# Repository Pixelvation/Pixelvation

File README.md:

**Pixelvation enables people to create high-quality LED art using open source tools**

This GitHub repository is the current home of Pixelvation and will be updated whenever there's some significant new development.  To get notified on significant new developments, set up an alert on new releases here, or follow [@PixelvationRGB on Twitter](https://twitter.com/PixelvationRgb).

I'll set up a forum or Discord server at some point, but for now, feel free to open a GitHub Issue, or post to [SmartMatrix Community](https://community.pixelmatix.com) if you have any questions or want to discuss anything.

## Open Source Early

I've released several open source products, where the open source files were published after the product was designed, manufactured, and at a distributor ready to purchase.  With my [latest crowdfunded product](https://www.crowdsupply.com/pixelmatix/smartled-shield-for-teensy-4) I realized how much time I had spent on marketing and logistics while prepping for and running the campaign - work I really dislike - relative to the creative and technical work that I really enjoy.  I also really enjoy sharing my projects and collaborating with other people, but releasing the product through a crowdfunding campaign delayed the start of fully sharing my project details and collaborating with other people by months.

With Pixelvation, I'm trying a new approach to sharing my projects: releasing projects as open source early on - well before I even have plans to release a project as a product - and making it easy for people to source the hardware themselves.  I'm designing my projects around components that are available from [JLCPCB's SMT Library](https://jlcpcb.com/parts) whenever possible, so if you want to try one of the hardware designs you just place an order with JLCPCB for 5+ pieces of assembled PCBs, and they'll be manufactured and shipped for a very reasonable price in under a week.

I'm releasing work-in-progress designs under a CC BY-NC-SA license.  Usually I don't release my designs with a "-NC" Non-Commercial license, and after the design is further along and ready for sale I'll change the license to CC BY-SA.  I'm conflicted about this and may change my mind later as designs released "-NC" aren't truly open source, but for now I'm being conservative and keeping the "-NC".

## Pixelvation Engine

The first tool in development now is the Pixelvation Engine, a small board dedicated to receiving a single stream of LED data via serial, and driving a lot of LEDs with that data.  The Engine will support driving HUB75 panels, or addressable LEDs.

As input, Pixelvation Engine accepts APA102 data at up to 5MHz, with 1-bit serial (like an APA102 LED), or up to 8-bit parallel.  The 1-bit serial input and CLK are buffered to accept up to 5V signals, but the remaining 7-bits parallel data must be driven at 3.3V only.

Pixelvation Engine has 16 outputs buffered to 5V levels, and an extra 3.3V output.  The outputs are arranged around the pinout of a HUB75 panel, so the board can be plugged into a HUB75 panel directly.  To instead drive up to 16 channels of addressable LEDs, Pixelvation Engine needs to be plugged into a simple breakout board.  Generic breakout boards will be designed and released in the future, but you can also design your own project-specific breakout board with space for the Pixelvation Engine, and the form factor and LED connectors your project actually needs.

Pixelvation Engine is based around the ESP32, which has enough RAM, CPU power, and DMA functionality to deal with a lot of LED data, and some unique I2S peripherals that allow for receiving a fast stream of serial or parallel LED data as input, and setting up another stream of parallel LED data as output.

To program Pixelvation Engine you need a USB-Serial adapter.  This functionality was purposely left off the board to save space and cost, and ideally these features are only needed when setting up a project.  The programming pins on the input side were designed around the ESP-01 pinout, so cheap ESP-01 programmers can be used.  Specifically [this ESP-01 programmer](https://www.amazon.com/ESP-01S-Programmer-Adapter-Wireless-4-5-5-5V/dp/B07V556Q82) ([cheaper on Aliexpress](https://www.aliexpress.com/item/32882742790.html))  has the most functionality and is the easiest to use on its own, is widely available, and with a couple jumper wires added becomes even more functional.

### Status

Currently Pixelvation Engine has been tested driving HUB75 panels up to 64x64 pixels, with APA102 input sources from [Pixelblaze (V1-V3)](https://www.crowdsupply.com/hencke-technologies/pixelblaze-v3), [WLED's sound reactive fork](https://github.com/atuline/WLED/) compiled with APA102 output and running on an ESP32 Dev board, and a Fadecandy-inspired USB to APA102 output board currently in development.

Pixelvation Engine uses [SmartMatrix Library 4.0's](https://github.com/pixelmatix/SmartMatrix) ESP32 support for driving HUB75 panels, and is able to drive a 64x64 HUB75 panel with 36-bit color, at 240Hz.  It's possible to drive a 128x64 HUB75 panel with the same color settings, but it requires additional hardware outside the Pixelvation Engine (this is being prototyped now).

The addressable LED output functionality hasn't been tested yet.  

The I2S Input code has some room for improvement, as it's very inefficient with memory right now, and can't keep up with a 4MHz 1-bit serial input when driving a 64x64 pixel output, but this is fixable.

[Click to watch demo video on Vimeo](https://vimeo.com/491391639/f8f3a9616e)

I ordered hardware version V0.1 assembled from [JLCPCB](https://jlcpcb.com) (10 pieces ~$70 plus shipping), and out of eight boards that I functionally tested, seven of them were working, and one has an undiagnosed problem.  The solder pad under the ESP32 should be using a [smaller squares for solder paste](https://twitter.com/GregDavill/status/1326309124565467136) instead of the one large square it's currently using, as the large square can lead to problems.  I don't plan on making any major changes to the pinout or functionality of the board at this point, but I may move to a 4-layer board, and shrink the board width by 0.1"/0.2" if possible.

### More Details

The hardware is posted in [Hardware/Pixelvation Engine](https://github.com/Pixelvation/Pixelvation/tree/master/Hardware/Pixelvation%20Engine), The Arduino sketch to drive HUB75 panels is [in a separate repo](https://github.com/Pixelvation/PixelvationEngine_HUB75) and more details are in  [the Wiki](https://github.com/Pixelvation/Pixelvation/wiki).

## About Pixelvation

I (Louis Beaudoin) created the open source [SmartMatrix Library](https://github.com/pixelmatix/SmartMatrix) and [SmartMatrix/SmartLED Shields](http://docs.pixelmatix.com/SmartMatrix/shieldref.html) for Teensy in 2014 under the name Pixelmatix and have been improving those projects ever since.  I thought a new brandname was appropriate for this series of new projects with a focus on both addressable LEDs and HUB75 LED matrix panels, and a focus on creating innovative tools for LED art.

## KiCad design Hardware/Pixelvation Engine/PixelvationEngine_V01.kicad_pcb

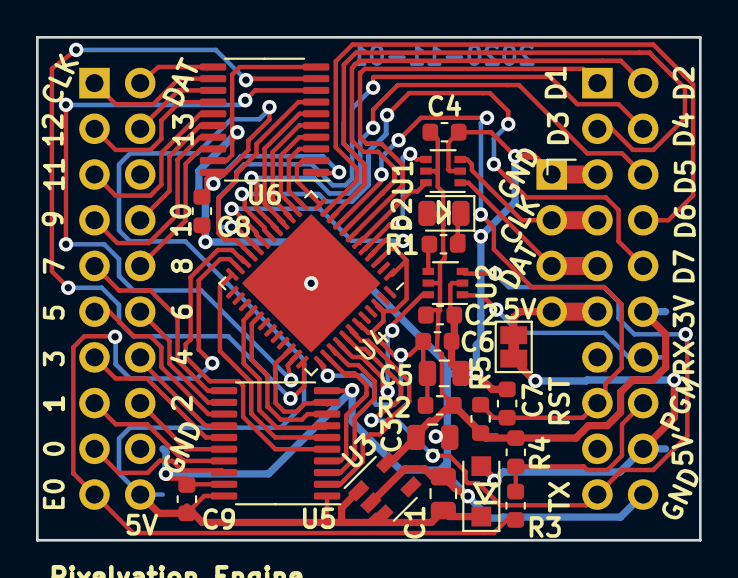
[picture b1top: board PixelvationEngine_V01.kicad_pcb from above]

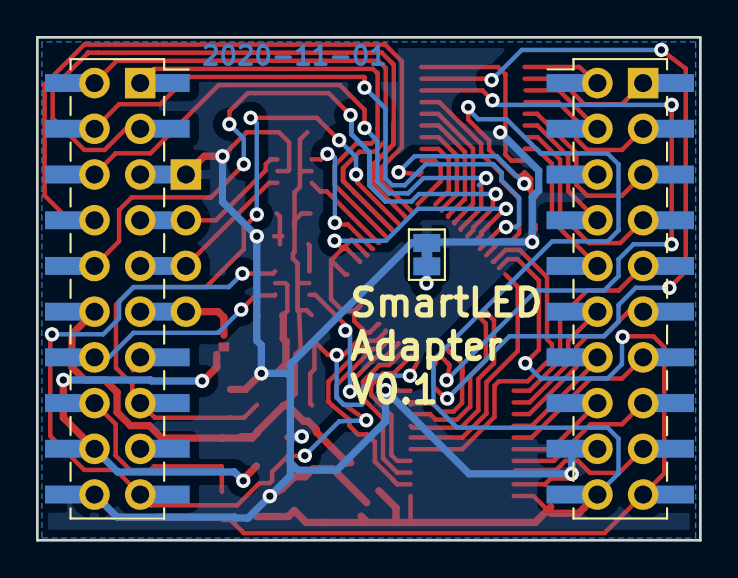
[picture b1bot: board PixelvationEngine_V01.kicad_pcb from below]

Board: 2 copper layers, 36.8 x 27.9 mm, 30 parts (4 on the bottom side), 61 nets.

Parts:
C1, C3, C5: 10uF; C_0805_2012Metric
C2, C4, C6, C7, C8, C9: 0.1uF; C_0603_1608Metric
D1: D; D_SOD-123F
D2: LED; LED_0805_2012Metric
J1: Conn_01x04; Harwin_M20-89004xx_1x04_P2.54mm_Horizontal
J3: Conn_01x04; PinHeader_1x04_P2.54mm_Vertical
J6: Conn_02x10_Odd_Even; PinHeader_2x10_P2.54mm_Vertical
J11: Conn_02x10_Odd_Even; PinHeader_2x10_P2.54mm_Vertical_SMD
J15: Conn_02x10_Odd_Even; PinSocket_2x10_P2.54mm_Vertical_SMD
J16: Conn_02x10_Odd_Even; PinSocket_2x10_P2.54mm_Vertical
JP1, JP2: SolderJumper_2_Bridged; SolderJumper-2_P1.3mm_Bridged_Pad1.0x1.5mm
R1: 1k; R_0603_1608Metric
R2: 0; R_0603_1608Metric
R3: 100; R_0603_1608Metric
R4, R5: 10k; R_0603_1608Metric
U1, U2: 74LVC2G17; SOT-363_SC-70-6
U3: AP2112K-3.3; SOT-23-5
U4: ESP32-PICO-D4; QFN-48-1EP_7x7mm_P0.5mm_EP5.45x5.45mm
U5, U6: 74HC245; TSSOP-20_4.4x6.5mm_P0.65mm

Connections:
+3V3: C2.1, C3.1, C4.1, D2.2, J15.12, J16.12, R2.2, R4.2, R5.2, U1.5, U2.5, U3.5
+5V: C1.1, C8.1, C9.1, D1.1, J6.20, J11.19, U3.1, U3.3, U5.1, U5.20, U6.1, U6.20
/3V3A: C5.1, C6.1, R2.1, U4.1, U4.3, U4.4, U4.19, U4.37, U4.43, U4.46
/APAIN_CLK: J1.2, J3.2, J15.7, J16.7, U1.3
/APAIN_DAT: J1.3, J3.3, J15.9, J16.9, U1.1
/BUFFER_00: U4.42, U5.2
/BUFFER_01: U4.39, U5.3
/BUFFER_02: U4.38, U5.4
/BUFFER_03: U4.22, U5.5
/BUFFER_04: U4.24, U5.6
/BUFFER_05: U4.28, U5.7
/BUFFER_06: U4.29, U5.8
/BUFFER_07: U4.34, U5.9
/BUFFER_08: U4.12, U6.2
/BUFFER_09: U4.13, U6.3
/BUFFER_10: U4.14, U6.4
/BUFFER_11: U4.15, U6.5
/BUFFER_12: U4.16, U6.6
/BUFFER_13: U4.21, U6.7
/BUFFER_APAOUT_CLK: U4.35, U6.8
/BUFFER_APAOUT_DAT: U4.36, U6.9
/EXTRA_GPIO0: J6.19, J11.20, R3.2, U4.23
/GPIO0_3V: J15.16, J16.16, R3.1, R4.1
/I2SIN_CLK_3V: U1.4, U4.5
/I2SIN_D0: U1.6, U4.6
/I2SIN_D1: J15.1, J16.1, U4.7
/I2SIN_D2: J15.2, J16.2, U4.8
/I2SIN_D3: J15.3, J16.3, U4.10
/I2SIN_D4: J15.4, J16.4, U4.20
/I2SIN_D5: J15.6, J16.6, U4.17
/I2SIN_D6: J15.8, J16.8, U4.11
/I2SIN_D7: J15.10, J16.10, U4.18
/LED_00: J6.17, J11.18, U5.18
/LED_01: J6.15, J11.16, U5.17
/LED_02: J6.16, J11.15, U5.16
/LED_03: J6.13, J11.14, U5.15
/LED_04: J6.14, J11.13, U5.14
/LED_05: J6.11, J11.12, U5.13
/LED_06: J6.12, J11.11, U5.12
/LED_07: J6.9, J11.10, U5.11
/LED_08: J6.10, J11.9, U6.18
/LED_09: J6.7, J11.8, U6.17
/LED_10: J6.8, J11.7, U6.16
/LED_11: J6.5, J11.6, U6.15
/LED_12: J6.3, J11.4, U6.14
/LED_13: J6.4, J11.3, U6.13
/LED_APAOUT_CLK: J6.1, J11.2, U6.12
/LED_APAOUT_DAT: J6.2, J11.1, U6.11
/RESET_3V: C7.1, J15.15, J16.15, R5.1, U4.9
/RX_3V: U2.6, U4.40
/RX_5V: J15.14, J16.14, U2.1
/TX: J15.19, J16.19, U2.3, U4.41
/VEXT: D1.2, J15.18, J16.18, JP1.2
GND: C1.2, C2.2, C3.2, C4.2, C5.2, C6.2, C7.2, C8.2, C9.2, J1.1, J3.1, J6.18, J11.17, J15.5, J15.20, J16.5, J16.20, JP2.2, U1.2, U2.2, U3.2, U5.10, U5.19, U6.10, U6.19
unnamed: D2.1, R1.2
unnamed: J1.4, J3.4, J15.11, J16.11, JP1.1
unnamed: J6.6, J11.5
unnamed: J15.13, J16.13
unnamed: J15.17, J16.17
unnamed: JP2.1, U4.49
unnamed: R1.1, U2.4

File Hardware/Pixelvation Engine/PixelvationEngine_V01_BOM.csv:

Comment,Designator,Footprint,LCSC
"10uF","C1,C3,C5","Capacitor_SMD:C_0805_2012Metric","C15850"
"0.1uF","C2,C4,C6,C7,C8,C9","Capacitor_SMD:C_0603_1608Metric","C14663"
"D","D1","Diode_SMD:D_SOD-123F","C223608"
"LED","D2","LED_SMD:LED_0805_2012Metric","C84256"
"Conn_01x04","J1","Connector_Harwin:Harwin_M20-89004xx_1x04_P2.54mm_Horizontal",""
"Conn_02x10_Odd_Even","J11","Connector_PinHeader_2.54mm:PinHeader_2x10_P2.54mm_Vertical_SMD",""
"Conn_02x10_Odd_Even","J15","Connector_PinSocket_2.54mm:PinSocket_2x10_P2.54mm_Vertical_SMD",""
"Conn_02x10_Odd_Even","J16","Connector_PinSocket_2.54mm:PinSocket_2x10_P2.54mm_Vertical",""
"Conn_01x04","J3","Connector_PinHeader_2.54mm:PinHeader_1x04_P2.54mm_Vertical",""
"Conn_02x10_Odd_Even","J6","Connector_PinHeader_2.54mm:PinHeader_2x10_P2.54mm_Vertical",""
"SolderJumper_2_Bridged","JP1,JP2","Jumper:SolderJumper-2_P1.3mm_Bridged_Pad1.0x1.5mm",""
"1k","R1","Resistor_SMD:R_0603_1608Metric","C21190"
"0","R2","Resistor_SMD:R_0603_1608Metric","C21189"
"100","R3","Resistor_SMD:R_0603_1608Metric","C22775"
"10k","R4,R5","Resistor_SMD:R_0603_1608Metric","C25804"
"74LVC2G17","U1,U2","Package_TO_SOT_SMD:SOT-363_SC-70-6","C50714"
"AP2112K-3.3","U3","Package_TO_SOT_SMD:SOT-23-5","C51118"
"ESP32-PICO-D4","U4","Package_DFN_QFN:QFN-48-1EP_7x7mm_P0.5mm_EP5.45x5.45mm","C193707"
"74HC245","U5,U6","Package_SO:TSSOP-20_4.4x6.5mm_P0.65mm","C173388"

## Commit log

2020-12-16 Add Pixelvation Engine V0.1 hardware files
2020-12-16 Add README
2020-12-16 no message

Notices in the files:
Hardware/Pixelvation Engine/PixelvationEngine_V01.kicad_pcb:
CC-BY-SA-NC Louis Beaudoin 2020
